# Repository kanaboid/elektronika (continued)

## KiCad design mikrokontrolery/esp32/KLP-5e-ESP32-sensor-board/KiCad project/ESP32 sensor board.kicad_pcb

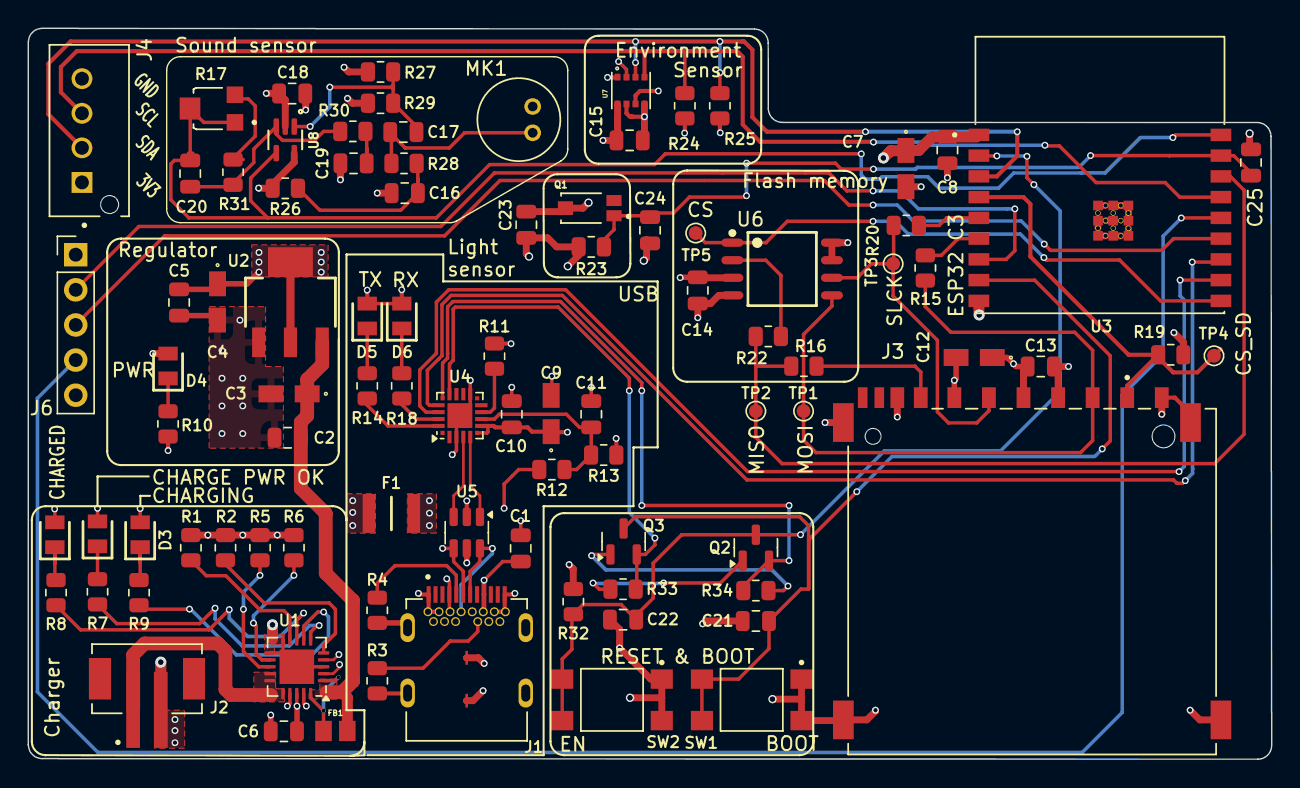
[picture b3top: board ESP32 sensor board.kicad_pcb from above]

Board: 4 copper layers, 89.9 x 52.8 mm, 90 parts (0 on the bottom side), 60 nets.

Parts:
C1, C2, C5, C8, C10, C13, C14, C15, C16, C18, C21, C23: 0.1u; C_0805_2012Metric
C3, C4, C7, C12: 10u; T491A
C6, C11, C22: 1u; C_0805_2012Metric
C9: 4.7u; T491A
C17, C24, C25: 10n; C_0805_2012Metric
C19: 10u; C_0805_2012Metric
C20: 100p; C_0805_2012Metric
D1, D4, D6: Red; LEDC2012X120N
D2, D5: Green; LEDC2012X120N
D3: Blue; LEDC2012X120N
F1: 0ZCH0110AF2E; FUSC3226X100N
FB1: FBMJ2125HM330-T; BEADC2012X105N
J1: USB_C_Receptacle; BELFUSE_SS-52400-002
J2: JST_2mm_LiPo; JST_B2B-PH-SM4-TB
J3: GSD090012SEU; AMPHENOL_GSD090012SEU
J4: B4B-XH-AM; JST_B4B-XH-AM__LF__SN_
J6: Conn_01x05; PinHeader_1x05_P2.54mm_Vertical
MK1: CMC-5042PF-AC; CUI_CMC-5042PF-AC
Q1: TEMT6000X01; TRANS_TEMT6000X01
Q2, Q3: BC817; SOT-23
R1, R2, R19, R23, R32, R33, R34: 10K; R_0805_2012Metric
R3, R4: 5k1; R_0805_2012Metric
R5, R26, R28: 2K; R_0805_2012Metric
R6: 20K; R_0805_2012Metric
R7, R8, R9: 470; R_0805_2012Metric
R10, R14, R18: 330; R_0805_2012Metric
R11, R30: 1K; R_0805_2012Metric
R12: 22K1; R_0805_2012Metric
R13: 47K5; R_0805_2012Metric
R15, R16, R20, R22: 50; R_0805_2012Metric
R17: 35WR100KLFTR; TRIM_35WR100KLFTR
R24, R25: 4K7; R_0805_2012Metric
R27, R29: 1M; R_0805_2012Metric
R31: 22K; R_0805_2012Metric
SW1, SW2: 1101NE; SW_TL3305AF260QG
TP1: Test MOSI; TestPoint_Pad_D1.0mm
TP2: Test MISO; TestPoint_Pad_D1.0mm
TP3: Test CLK; TestPoint_Pad_D1.0mm
TP4: TEST CS_SD; TestPoint_Pad_D1.0mm
TP5: TEST CS; TestPoint_Pad_D1.0mm
U1: MCP73871; QFN-20-1EP_4x4mm_P0.5mm_EP2.5x2.5mm
U2: LM1117MPX-3.3_NOPB; VREG_LM1117MPX-3.3
U3: ESP32-C3-WROOM-02-H4; MODULE_ESP32-C3-WROOM-02-H4
U4: CP2102N-A02-GQFN20; SiliconLabs_QFN-20-1EP_3x3mm_P0.5mm_EP1.8x1.8mm
U5: USBLC6-2SC6; SOT-23-6
U6: W25Q32JVSSIQ; SOIC127P790X216-8N
U7: BME280; PSON65P250X250X100-8N
U8: MAX4466EXK+T; SOT65P210X110-5N

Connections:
3.3V: C4.1 (+), C5.1, C7.1 (+), C8.1, C9.1 (+), C10.1, C12.1 (+), C13.2, C14.1, C15.2, C18.1, C23.1, D4.2 (A), D5.2 (A), D6.2 (A), J3.4 (VDD1), J4.1, J6.1, Q1.3, R11.1, R19.2, R24.1, R25.1, R26.2, R27.2, R32.2, U2.2 (VOUT_2), U2.4 (VOUT_4), U3.1 (3V3), U4.6 (VDD), U4.7 (VREGIN), U6.3 (~WP(IO2)), U6.7 (~HOLD/~RESET(IO3)), U6.8 (VCC), U7.2 (CSB), U7.6 (VDDIO), U7.8 (VDD), U8.5 (VCC)
+5V: C2.1, C3.1 (+), FB1.1, U2.3 (VIN)
/+5V_USB: C6.1, D1.2 (A), D2.2 (A), D3.2 (A), F1.2, U1.2 (VPCC), U1.4 (PROG2), U1.17 (CE), U1.18 (IN), U1.19 (IN)
/CHARGED: R8.1, U1.8 (STAT1/~LBO)
/CHARGING: R9.1, U1.7 (STAT2)
/CHARGING_POWER_GOOD: R7.1, U1.6 (~PG)
/ESP32-C3-02/BOOT: C21.1, Q3.3 (C), SW1.3, SW1.4, U3.8 (IO9)
/ESP32-C3-02/CS: TP5.1, U3.10 (IO10), U6.1 (~CS)
/ESP32-C3-02/CS_SD: J3.1 (CD/DAT3), R19.1, TP4.1, U3.4 (IO5)
/ESP32-C3-02/DTS: Q3.2 (E), R33.1, U4.15 (~CTS)
/ESP32-C3-02/EN: C22.1, Q2.3 (C), R32.1, SW2.3, SW2.4, U3.2 (EN)
/ESP32-C3-02/GPIO8: J6.2, U3.7 (IO8)
/ESP32-C3-02/GPIO18: J6.3, U3.13 (IO18)
/ESP32-C3-02/GPIO19: J6.4, U3.14 (IO19)
/ESP32-C3-02/MIC_OUT: C20.2, R17.1, R17.2, U3.18 (IO0), U8.4 (OUT)
/ESP32-C3-02/MISO_DO: R16.2, R22.1, TP2.1, U3.16 (IO2)
/ESP32-C3-02/MOSI_DI: J3.2 (CMD), R15.1, TP1.1, U6.5 (DI(IO0))
/ESP32-C3-02/PHOTO_C: C24.1, C25.1, Q1.1, R23.1, U3.17 (IO1)
/ESP32-C3-02/RTS: Q2.2 (E), R34.1, U4.16 (~RTS)
/ESP32-C3-02/RX_TX: U3.12 (TXD), U4.17 (RXD)
/ESP32-C3-02/SCL: J4.3, R24.2, U3.15 (IO3), U7.4 (SCK)
/ESP32-C3-02/SCLK: J3.5 (CLK), R20.1, TP3.1, U6.6 (CLK)
/ESP32-C3-02/SDA: J4.2, R25.2, U3.3 (IO4), U7.3 (SDI)
/ESP32-C3-02/TX_RX: U3.11 (RXD), U4.18 (TXD)
/ESP32-C3-02/USB_D+: U4.4 (D+), U5.3 (I/O2)
/ESP32-C3-02/USB_D-: U4.5 (D-), U5.1 (I/O1)
/PWR_LED: D4.1 (K), R10.2
/USB_DN: J1.A7 (DN1), J1.B7 (DN2), U5.6 (I/O1)
/USB_DP: J1.A6 (DP1), J1.B6 (DP2), U5.4 (I/O2)
/VBAT: J2.1, U1.14 (V_{BAT}), U1.15 (V_{BAT}), U1.16 (V_{BAT_SENSE})
/VBUS: C1.1, F1.1, J1.A4 (VBUSA1), J1.A9 (VBUSA2), J1.B4 (VBUSB1), J1.B9 (VBUSB2), R12.1, U5.5 (VBUS)
GND: C1.2, C2.2, C3.2 (-), C4.2 (-), C5.2, C6.2, C7.2 (-), C8.2, C9.2 (-), C10.2, C11.2, C12.2 (-), C13.1, C14.2, C15.1, C16.2, C18.2, C19.1, C21.2, C22.2, C23.2, C24.2, C25.2, J1.A1 (GNDA1), J1.A12 (GNDA2), J1.B1 (GNDB1), J1.B12 (GNDB2), J1.G1 (GND/SHIELD), J1.G2 (GND/SHIELD), J1.G3 (GND/SHIELD), J1.G4 (GND/SHIELD), J1.S1 (GND/SHIELD), J1.S2 (GND/SHIELD), J1.S3 (GND/SHIELD), J1.S4 (GND/SHIELD), J2.2, J3.3 (VSS1), J3.6 (VSS2), J3.8 (DAT1), J3.9 (DAT2), J3.G1 (SHIELD_GND), J3.G2 (SHIELD_GND), J3.G3 (SHIELD_GND), J3.G4 (SHIELD_GND), J4.4, J6.5, MK1.GND, R1.2, R2.2, R3.2, R4.2, R5.2, R6.2, R10.1, R13.2, R23.2, R29.1, SW1.1, SW1.2, SW2.1, SW2.2, U1.3 (SEL), U1.10 (V_{SS}), U1.11 (V_{SS}), U1.21 (V_{SS}), U2.1 (GND), U3.9 (GND), U3.19 (GND), U3.20 (GND), U3.21 (GND), U3.22 (GND), U3.23 (GND), U3.24 (GND), U3.25 (GND), U3.26 (GND), U3.27 (GND), U3.28 (GND), U3.29 (GND), U3.30 (GND), U3.31 (GND), U3.32 (GND), U3.33 (GND), U3.34 (GND), U3.35 (GND), U3.36 (GND), U3.37 (GND), U3.38 (GND), U3.39 (GND), U4.3 (GND), U4.12 (GND), U4.21 (GND), U5.2 (GND), U6.4 (GND), U7.1 (GND), U7.5 (SDO), U7.7 (GND), U8.2 (GND)
unnamed: C16.1, R26.1, R28.2
unnamed: C17.2, MK1.OUT, R28.1
unnamed: C19.2, R30.1
unnamed: D1.1 (K), R7.2
unnamed: D2.1 (K), R8.2
unnamed: D3.1 (K), R9.2
unnamed: D5.1 (K), R14.2
unnamed: D6.1 (K), R18.2
unnamed: FB1.2, U1.1 (OUT), U1.20 (OUT)
unnamed: J1.A5 (CC1), R4.1
unnamed: J1.B5 (CC2), R3.1
unnamed: J3.7 (DAT0), R16.1
unnamed: Q2.1 (B), R33.2
unnamed: Q3.1 (B), R34.2
unnamed: R17.3, R31.2
unnamed: R5.1, U1.13 (PROG1)
unnamed: R6.1, U1.12 (PROG3)
unnamed: R2.1, U1.5 (THERM)
unnamed: R1.1, U1.9 (~TE)
unnamed: R20.2, U3.5 (IO6)
unnamed: R15.2, U3.6 (IO7)
unnamed: C11.1, R12.2, R13.1, U4.8 (VBUS)
unnamed: R11.2, U4.9 (~RST)
unnamed: R18.1, U4.19 (~RXT/GPIO.3)
unnamed: R14.1, U4.20 (~TXT/GPIO.2)
unnamed: R22.2, U6.2 (DO(IO1))
unnamed: C17.1, R27.1, R29.2, U8.1 (IN+)
unnamed: C20.1, R30.2, R31.1, U8.3 (IN-)

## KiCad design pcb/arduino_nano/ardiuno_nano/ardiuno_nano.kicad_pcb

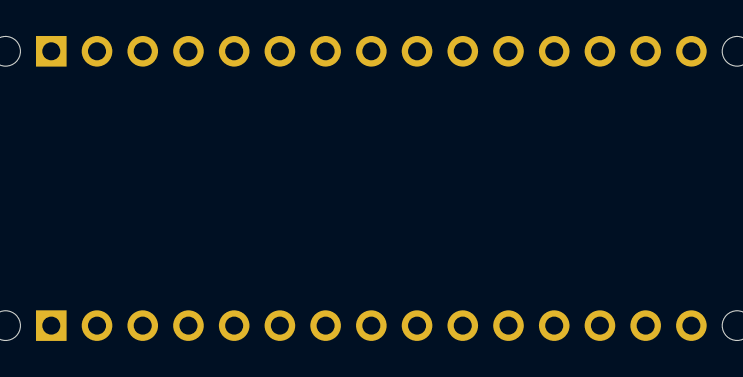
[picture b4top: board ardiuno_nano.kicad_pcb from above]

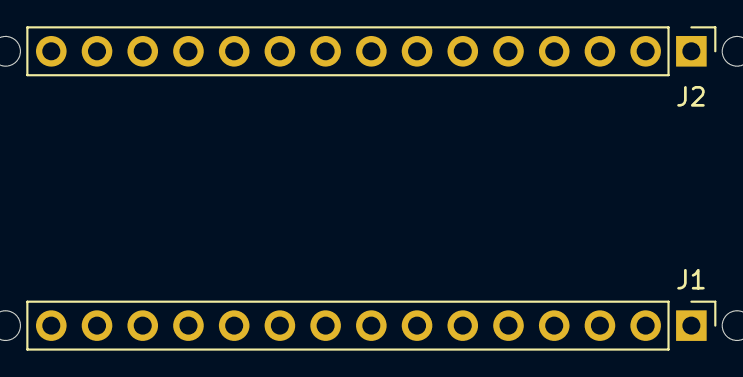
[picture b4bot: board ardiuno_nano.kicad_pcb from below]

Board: 2 copper layers, 6 parts (2 on the bottom side), 2 nets, no tracks yet.

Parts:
J1: Analog; PinHeader_1x15_P2.54mm_Vertical
J2: Digital; PinHeader_1x15_P2.54mm_Vertical
MH1, MH2, MH3, MH4: MountingHole_65mil

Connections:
/~RESET: J1.13, J2.13
GND: J1.14, J2.12

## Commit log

2026-01-03 Init commit
2026-01-03 Add power
2026-01-03 gitingnore
2026-01-03 resync lap-to-pc
2026-01-03 Add backup of espander_100x_i2c project files from January 3, 2026
2026-01-03 Add fp-lib-table for Arduino mounting hole library
    - Created a new fp-lib-table file for the Arduino_MountingHole library.
    - Defined library name, type, URI, and other metadata.
2026-01-04 PDF - PCB design mistakes
2026-01-04 Remove /rozne/ from .gitignore
2026-01-07 Refactor code structure and remove redundant sections for improved readability and maintainability
2026-01-09 Add initial DRU file for espander_100x_i2c PCB design
2026-01-12 Refactor code structure for improved readability and maintainability
2026-01-12 RESYNC
2026-01-15 add techexplorations.com pdfs
2026-01-15 gitignore update
2026-01-15 gitignore
2026-01-15 gitignore#2
2026-01-16 pdf update
2026-01-17 esp32 Arduino merge
2026-01-19 Ekspander update
2026-01-19 repair git
2026-01-19 esp32 reupload
2026-01-19 ekspander resync
2026-01-22 Ekspander 100x - zasilanie 3V3
2026-01-23 Ekspander U2 - U3 - U4 update
2026-01-27 Ekspander U5 - U6 update
2026-01-29 Ekspander 24V update
2026-02-03 Ekspander 100x - PCB layout V1
2026-02-04 Ekspander 100x - PCB layout V2
2026-02-04 Ekspander 100x - rerouting
2026-02-04 0.65mm
2026-02-05 Ekspander 100x - finish J
2026-02-05 Remove temporary and backup files, update component properties in the I2C ekspander PCB design, and enhance the CSV with additional component details.
2026-02-06 Tech Explorations
2026-02-13 Ekspander 100x - UART-USB
2026-02-14 Ekspander 100x - LEDs
2026-02-14 Ekspander 100x - adresacja I2C - MCP23017
2026-02-17 Ekspander 100x - mounting holes - rerouting
2026-02-17 Ekspander 100x - diagnostic LEDs
2026-02-18 Ekspander 100x - RS485
2026-02-19 Ekspander 100x - RESET - BOOT - switches
2026-04-13 Add BlinkRGB example for controlling onboard RGB LED with WiFi support for c3-zero
    - Implemented a sketch to control an RGB LED using an ESP board.
    - Added WiFi connectivity to allow remote control of the LED via HTTP requests.
    - Defined a sequence of LED color changes with adjustable brightness.
    - Included handling for turning the LED on and off through web requests.
    - Added status monitoring for the control pin and WiFi connection.
2026-04-25 Remove obsolete CSV file for door event logging
2026-04-25 Enhance ESP32 project setup and main functionality
    - Updated VSCode settings to include UART flash type.
    - Modified CMakeLists.txt to register additional source files: led_status.c, wifi_app.c, and web_ui.c.
    - Expanded main.c to initialize LED status, Wi-Fi, and web UI with logging for better debugging.
2026-04-26 Refactor Wi-Fi configuration in wifi_app.c to use defined constants
    - Replaced hardcoded SSID and password with defined constants for better maintainability.
    - Updated logging to reflect the new constant usage for Wi-Fi connection status.
2026-04-26 Update Wi-Fi configuration to support open networks and improve logging
    - Added support for open networks by checking if the Wi-Fi password is empty.
    - Updated logging to provide clearer information about the Wi-Fi connection status, including whether the network is open or secured.
    - Replaced hardcoded SSID and password references with Kconfig constants for better maintainability.
2026-04-26 Add DS18B20 sensor support and update dependencies
    - Integrated DS18B20 sensor functionality into the project, including new source files and Kconfig options for GPIO configuration.
    - Updated CMakeLists.txt to register the DS18B20 application and its dependencies.
    - Enhanced web UI to display DS18B20 sensor readings, including temperature and sensor status.
    - Updated dependencies.lock and idf_component.yml to include espressif/ds18b20 and espressif/onewire_bus components.
2026-04-27 Adresy DS18B20 - dom
2026-04-27 Add additional DS18B20 sensor addresses
    - Added new sensor addresses DS003, DS004, and DS005 to the DS18B20 configuration file for enhanced temperature monitoring capabilities.
2026-04-27 Add A01NYUB sensor support and update web UI
    - Integrated A01NYUB UART distance sensor functionality, including new Kconfig options for UART configuration.
    - Updated CMakeLists.txt to register the A01NYUB application and its dependencies.
    - Enhanced web UI to display A01NYUB sensor readings and status, including mode configuration options.
    - Added new API endpoints for A01NYUB mode management and sensor data retrieval.
2026-04-28 Update RGB_BUILTIN pin definition for BlinkRGB example to match hardware configuration
2026-05-06 Update VSCode settings to change the COM port from COM3 to COM5 for ESP32 S3 WROOM 1 configuration
2026-05-15 Licznik Audi A3 8L FL
2026-05-31 Add Wi-Fi and NTP configuration for A3 Cluster
    - Enabled Wi-Fi support and configured NTP server in sdkconfig.defaults.
    - Updated CMakeLists.txt to include new source file for Wi-Fi and time management.
    - Enhanced main.c with additional functionality for handling Wi-Fi and time synchronization.
